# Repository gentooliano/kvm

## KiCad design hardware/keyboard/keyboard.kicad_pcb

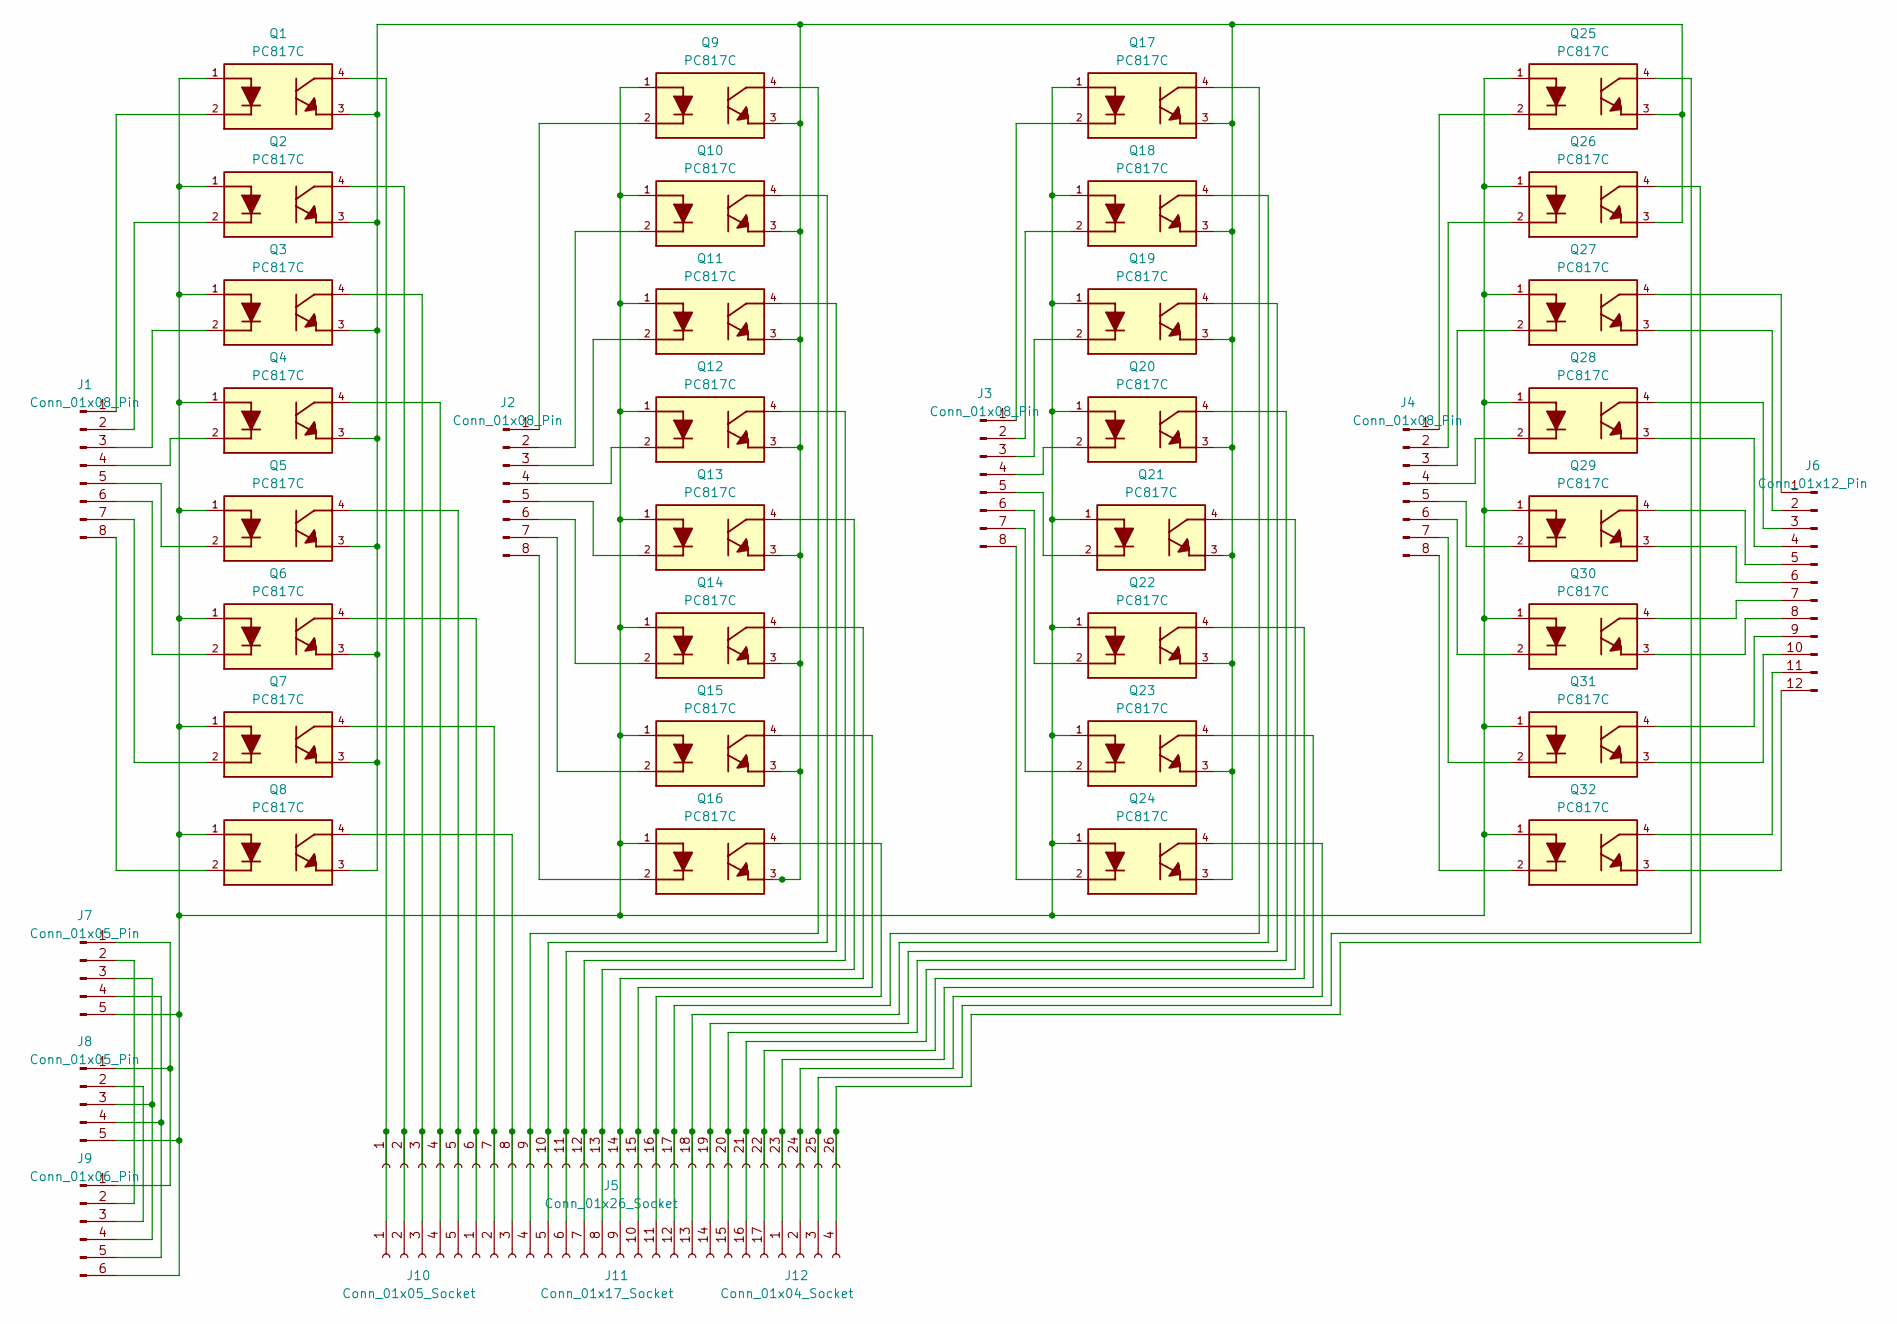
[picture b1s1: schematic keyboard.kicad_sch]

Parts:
J1, J2, J3, J4: Conn_01x08_Pin; PinHeader_1x08_P2.54mm_Vertical
J5: Conn_01x26_Socket; PinHeader_1x26_P2.54mm_Vertical
J6: Conn_01x12_Pin; PinHeader_1x12_P2.54mm_Vertical
J7, J8: Conn_01x05_Pin; PinHeader_1x05_P2.54mm_Vertical
J9: Conn_01x06_Pin; PinHeader_1x06_P2.54mm_Vertical
J10: Conn_01x05_Socket; PinSocket_1x05_P2.00mm_Vertical
J11: Conn_01x17_Socket; PinSocket_1x17_P2.00mm_Vertical
J12: Conn_01x04_Socket; PinSocket_1x04_P2.00mm_Vertical
Q1, Q2, Q3, Q4, Q5, Q6, Q7, Q8, Q9, Q10, Q11, Q12, Q13, Q14, Q15, Q16, Q17, Q18, Q19, Q20, Q21, Q22, Q23, Q24, Q25, Q26, Q27, Q28, Q29, Q30, Q31, Q32: PC817C; DIP762W50P254L650H458Q4B; PARTREV N/A

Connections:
unnamed: J1.1, Q1.2
unnamed: J1.2, Q2.2
unnamed: J1.3, Q3.2
unnamed: J1.4, Q4.2
unnamed: J1.5, Q5.2
unnamed: J1.6, Q6.2
unnamed: J1.7, Q7.2
unnamed: J1.8, Q8.2
unnamed: J2.1, Q9.2
unnamed: J2.2, Q10.2
unnamed: J2.3, Q11.2
unnamed: J2.4, Q12.2
unnamed: J2.5, Q13.2
unnamed: J2.6, Q14.2
unnamed: J2.7, Q15.2
unnamed: J2.8, Q16.2
unnamed: J3.1, Q17.2
unnamed: J3.2, Q18.2
unnamed: J3.3, Q19.2
unnamed: J3.4, Q20.2
unnamed: J3.5, Q21.2
unnamed: J3.6, Q22.2
unnamed: J3.7, Q23.2
unnamed: J3.8, Q24.2
unnamed: J4.1, Q25.2
unnamed: J4.2, Q26.2
unnamed: J4.3, Q27.2
unnamed: J4.4, Q28.2
unnamed: J4.5, Q29.2
unnamed: J4.6, Q30.2
unnamed: J4.7, Q31.2
unnamed: J4.8, Q32.2
unnamed: J6.1, Q27.4
unnamed: J6.2, Q27.3
unnamed: J6.3, Q28.4
unnamed: J6.4, Q28.3
unnamed: J6.5, Q29.4
unnamed: J6.6, Q29.3
unnamed: J6.7, Q30.4
unnamed: J6.8, Q30.3
unnamed: J6.9, Q31.4
unnamed: J6.10, Q31.3
unnamed: J6.11, Q32.4
unnamed: J6.12, Q32.3
unnamed: J7.1, J8.1, J9.1
unnamed: J7.2, J9.2
unnamed: J7.3, J8.3, J9.4
unnamed: J7.4, J8.4, J9.5
unnamed: J7.5, J8.5, J9.6, Q1.1, Q2.1, Q3.1, Q4.1, Q5.1, Q6.1, Q7.1, Q8.1, Q9.1, Q10.1, Q11.1, Q12.1, Q13.1, Q14.1, Q15.1, Q16.1, Q17.1, Q18.1, Q19.1, Q20.1, Q21.1, Q22.1, Q23.1, Q24.1, Q25.1, Q26.1, Q27.1, Q28.1, Q29.1, Q30.1, Q31.1, Q32.1
unnamed: J8.2, J9.3
unnamed: J5.1, J10.1, Q1.4
unnamed: J5.2, J10.2, Q2.4
unnamed: J5.3, J10.3, Q3.4
unnamed: J5.4, J10.4, Q4.4
unnamed: J5.5, J10.5, Q5.4
unnamed: J5.6, J11.1, Q6.4
unnamed: J5.7, J11.2, Q7.4
unnamed: J5.8, J11.3, Q8.4
unnamed: J5.9, J11.4, Q9.4
unnamed: J5.10, J11.5, Q10.4
unnamed: J5.11, J11.6, Q11.4
unnamed: J5.12, J11.7, Q12.4
unnamed: J5.13, J11.8, Q13.4
unnamed: J5.14, J11.9, Q14.4
unnamed: J5.15, J11.10, Q15.4
unnamed: J5.16, J11.11, Q16.4
unnamed: J5.17, J11.12, Q17.4
unnamed: J5.18, J11.13, Q18.4
unnamed: J5.19, J11.14, Q19.4
unnamed: J5.20, J11.15, Q20.4
unnamed: J5.21, J11.16, Q21.4
unnamed: J5.22, J11.17, Q22.4
unnamed: J5.23, J12.1, Q23.4
unnamed: J5.24, J12.2, Q24.4
unnamed: J5.25, J12.3, Q25.4
unnamed: J5.26, J12.4, Q26.4
unnamed: Q1.3, Q2.3, Q3.3, Q4.3, Q5.3, Q6.3, Q7.3, Q8.3, Q9.3, Q10.3, Q11.3, Q12.3, Q13.3, Q14.3, Q15.3, Q16.3, Q17.3, Q18.3, Q19.3, Q20.3, Q21.3, Q22.3, Q23.3, Q24.3, Q25.3, Q26.3

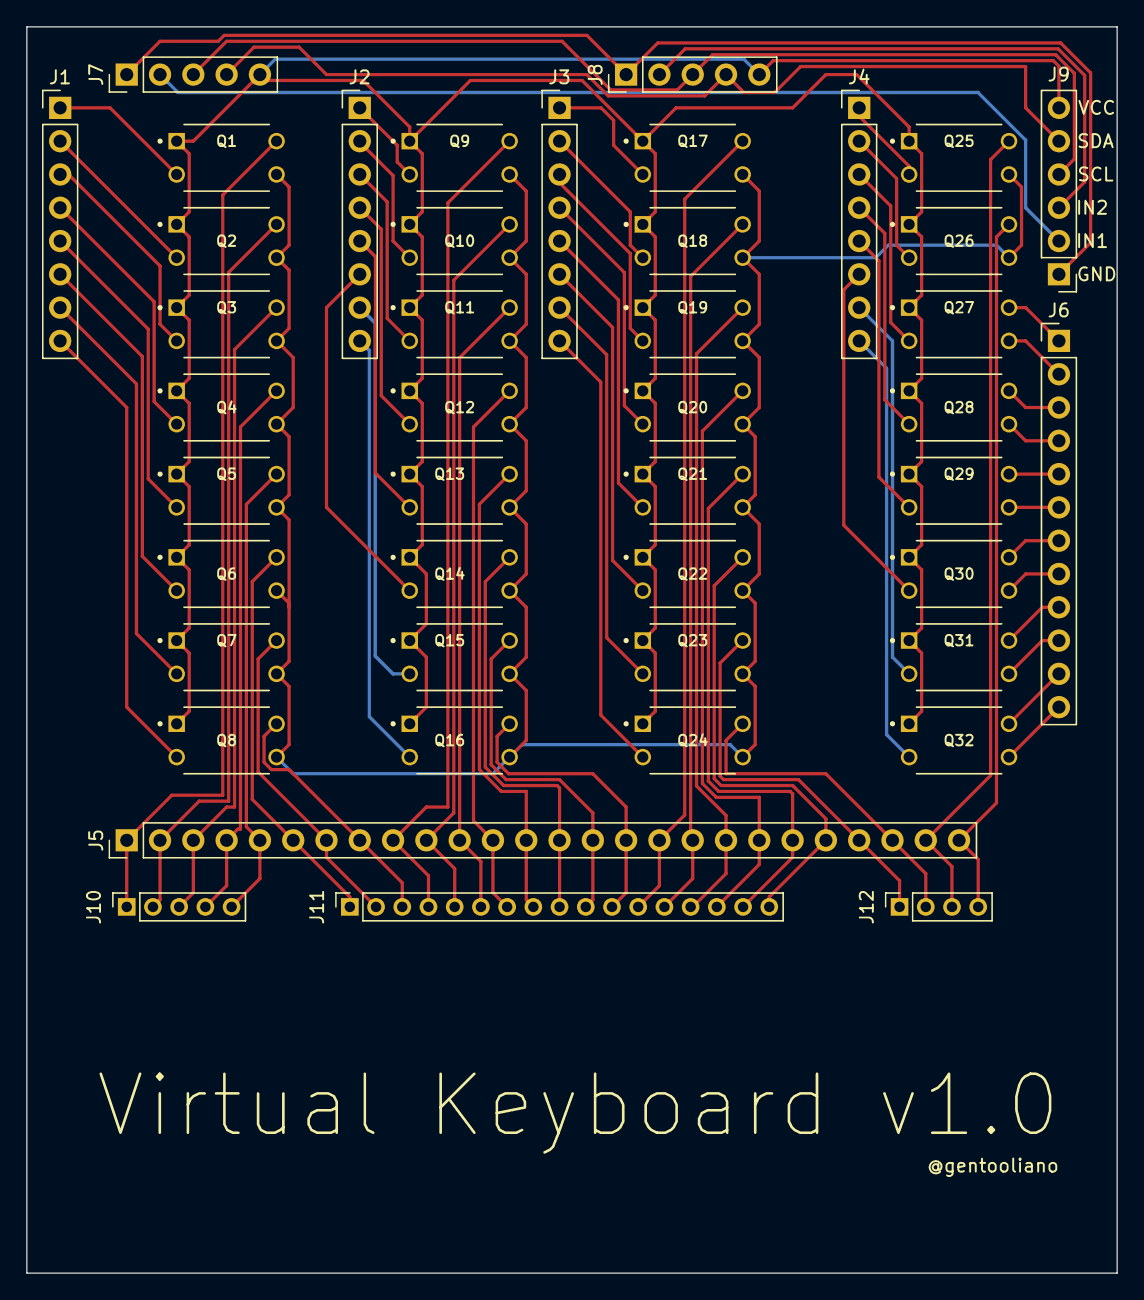
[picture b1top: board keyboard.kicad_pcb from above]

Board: 2 copper layers, 83.2 x 95.1 mm, 44 parts (0 on the bottom side), 77 nets.

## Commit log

2023-11-07 Add PC817C data
2023-11-07 Change sources structure
2023-11-07 Clean root folder
2023-11-07 Add .idea folder in old sources
2023-11-07 Add main project
2023-11-08 Updates v1.0
2023-11-14 Update 1411231715
2023-11-17 Update 151120232000
